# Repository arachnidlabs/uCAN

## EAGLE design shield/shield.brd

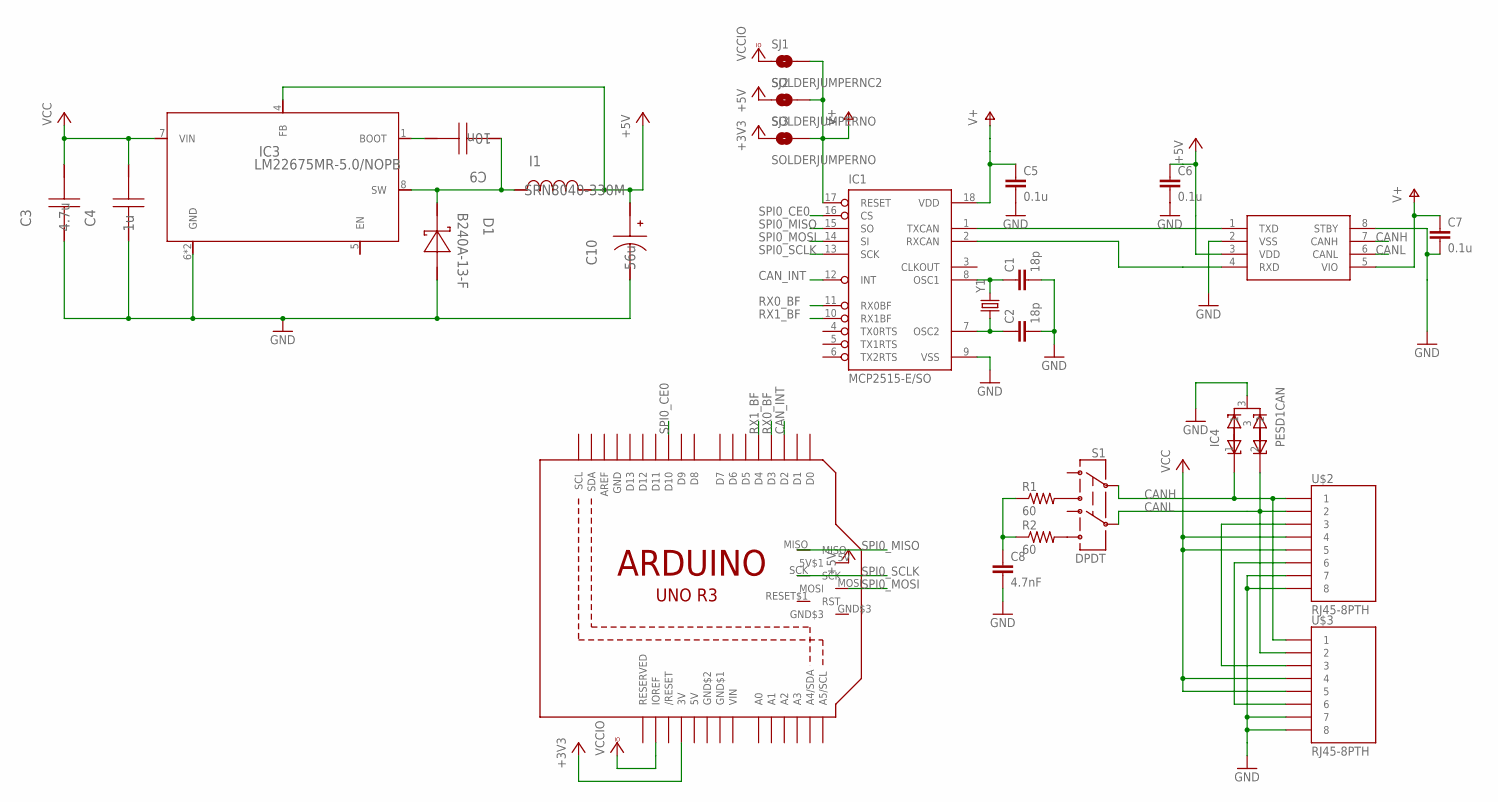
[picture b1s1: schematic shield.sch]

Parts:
C1, C2: 18p; 0603-CAP
C3: 4.7u; 1206
C4: 1u; 0805
C5, C6, C7: 0.1u; 0603-CAP
C8: 4.7nF; 0603-CAP
C9: 10n; 0805
C10: 56u; SM_RADIAL_6.3AMM
D1: B240A-13-F; SMA
I1: SRN8040-330M; SRN8040
IC1: MCP2515-E/SO; SO18L
IC2: MCP2562; SO08
IC3: LM22675MR-5.0/NOPB; MRA08B
IC4: PESD1CAN; SOT23
R1, R2: 60; 0603-RES
S1: DPDT; AYZ0202
SJ1: SOLDERJUMPERNC2; SJ_2S-NOTRACE
SJ2, SJ3: SOLDERJUMPERNO; SJ_2S-NO
U$1: ARDUINO_R3_ICSPNODIM; ARDUINOR3_ICSP_NODIM
U$2, U$3: RJ45-8PTH; RJ45-8
Y1: CRYSTAL5X3; CRYSTAL-SMD-5X3

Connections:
5V: U$1.+5V (5V)
+3V3: SJ3.1, U$1.3V
+5V: C6.1, C10.1 (+), I1.1, IC2.3 (VDD), IC3.4 (FB), SJ2.1, U$1.5V (5V$1)
CANH: IC2.7 (CANH), IC4.1, S1.2, U$2.1, U$3.1
CANL: IC2.6 (CANL), IC4.2, S1.5, U$2.2, U$3.2
CAN_INT: IC1.12 (INT), U$1.D2
GND: C1.2, C2.2, C3.2, C4.2, C5.2, C6.2, C7.2, C8.2, C10.2 (-), D1.2 (A), IC1.9 (VSS), IC2.2 (VSS), IC2.8 (STBY), IC3.6 (GND), IC3.EPAD (GND), IC4.3, U$1.GND, U$2.7, U$2.8, U$3.7, U$3.8
GND$1: U$1.GND$1
GND$2: U$1.GND$2
unnamed: R1.2, S1.3
unnamed: R2.2, S1.6
unnamed: C1.1, IC1.8 (OSC1), Y1.3 (2)
unnamed: C2.1, IC1.7 (OSC2), Y1.1
unnamed: C8.1, R1.1, R2.1
unnamed: U$2.6, U$3.6
unnamed: U$2.3, U$3.3
unnamed: C9.1, IC3.1 (BOOT)
RX0_BF: IC1.11 (RX0BF), U$1.D3
RX1_BF: IC1.10 (RX1BF), U$1.D4
RXCAN: IC1.2 (RXCAN), IC2.4 (RXD)
SPI0_CE0: IC1.16 (CS), U$1.D10
SPI0_MISO: IC1.15 (SO), U$1.MISO
SPI0_MOSI: IC1.14 (SI), U$1.MOSI
SPI0_SCLK: IC1.13 (SCK), U$1.SCK
SWOUT: C9.2, D1.1 (K), I1.2, IC3.8 (SW)
TXCAN: IC1.1 (TXCAN), IC2.1 (TXD)
V+: C5.1, C7.1, IC1.17 (RESET), IC1.18 (VDD), IC2.5 (VIO), SJ1.2, SJ2.2, SJ3.2
VCC: C3.1, C4.1, IC3.7 (VIN), U$2.4, U$2.5, U$3.4, U$3.5
VCCIO: SJ1.1, U$1.IOREF
VIN: U$1.VIN

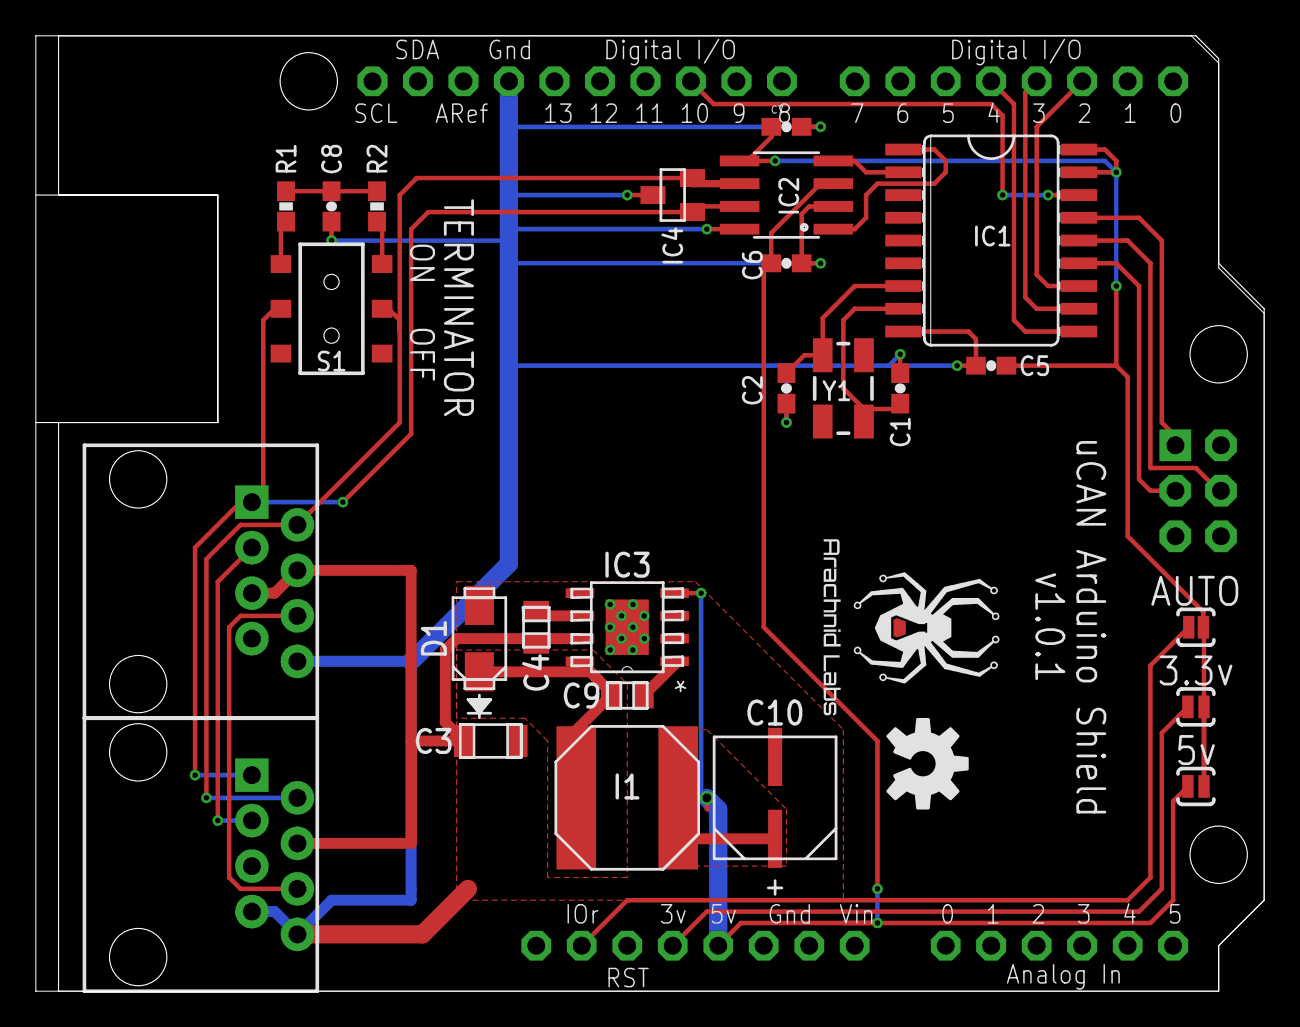
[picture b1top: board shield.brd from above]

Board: 2 copper layers, 68.6 x 53.3 mm, 28 parts (0 on the bottom side), 26 nets.

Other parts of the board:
U$4: ARACHNID_LABS_LOGO_SM
U$5: OSHW-LOGO-M

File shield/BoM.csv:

"Part";"Value";"Device";"Package";"Description";"PROD_ID";"VALUE";
"C1";"18p";"CAP0603-CAP";"0603-CAP";"Capacitor";"";"";
"C2";"18p";"CAP0603-CAP";"0603-CAP";"Capacitor";"";"";
"C3";"";"CAP_POLG";"PANASONIC_G";"Capacitor Polarized";"";"";
"C4";"";"CAP_POLE";"PANASONIC_E";"Capacitor Polarized";"";"";
"C5";"0.1u";"CAP0603-CAP";"0603-CAP";"Capacitor";"";"";
"C6";"0.1u";"CAP0603-CAP";"0603-CAP";"Capacitor";"";"";
"C7";"0.1u";"CAP0603-CAP";"0603-CAP";"Capacitor";"";"";
"C8";"4.7nF";"CAP0603-CAP";"0603-CAP";"Capacitor";"";"";
"D1";"";"DIODESMA-ALT";"SMA-DIODE_ALT";"Diode";"";"";
"IC1";"MCP2515-E/SO";"MCP2515-E/SO";"SO18L";"";"";"";
"IC2";"MCP2562";"MCP2562";"SO08";"CAN transceiver";"";"";
"IC3";"LM2595NDH";"LM2595NDH";"TO263-5";"";"";"";
"IC4";"PESD1CAN";"PESD1CAN";"SOT23";"";"";"";
"L1";"MSS1260";"MSS1260";"MSS1260";"";"";"";
"R1";"60";"RESISTOR0603-RES";"0603-RES";"Resistor";"";"";
"R2";"60";"RESISTOR0603-RES";"0603-RES";"Resistor";"";"";
"S1";"DPDT";"SWITCH-DPDTAYZ0202";"AYZ0202";"DPDT Version of the COM-00597";"SWCH-08179";"DPDT";
"SJ1";"SOLDERJUMPERNC2";"SOLDERJUMPERNC2";"SJ_2S-NOTRACE";"Solder Jumper";"";"";
"SJ2";"SOLDERJUMPERNO";"SOLDERJUMPERNO";"SJ_2S-NO";"Solder Jumper";"";"";
"SJ3";"SOLDERJUMPERNO";"SOLDERJUMPERNO";"SJ_2S-NO";"Solder Jumper";"";"";
"U$1";"ARDUINO_R3_ICSP";"ARDUINO_R3_ICSP";"ARDUINOR3_ICSP";"";"";"";
"U$2";"RJ45-8PTH";"RJ45-8PTH";"RJ45-8";"RJ45 Jack";"";"";
"U$3";"RJ45-8PTH";"RJ45-8PTH";"RJ45-8";"RJ45 Jack";"";"";
"Y1";"";"CRYSTAL5X3";"CRYSTAL-SMD-5X3";"Various standard crystals. Proven footprints. Spark Fun Electronics SKU : COM-00534";"";"";

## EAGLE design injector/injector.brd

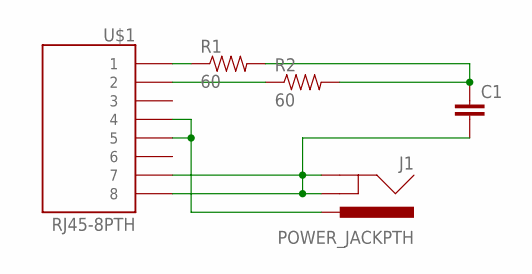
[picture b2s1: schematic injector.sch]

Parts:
C1: CAP0603-CAP; 0603-CAP
J1: POWER_JACKPTH; POWER_JACK_PTH
R1, R2: 60; 0603-RES
U$1: RJ45-8PTH; RJ45-8

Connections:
unnamed: R1.1, U$1.1
unnamed: R2.1, U$1.2
unnamed: J1.PWR, U$1.4, U$1.5
unnamed: C1.2, J1.GND, J1.GNDBREAK, U$1.7, U$1.8
unnamed: C1.1, R1.2, R2.2

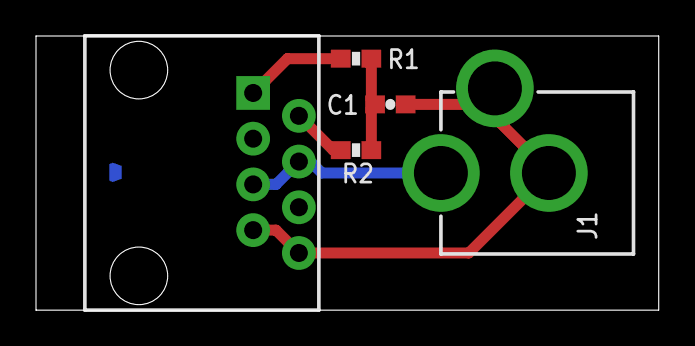
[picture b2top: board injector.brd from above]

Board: 2 copper layers, 34.6 x 15.2 mm, 6 parts (1 on the bottom side), 5 nets.

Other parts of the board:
U$2: ARACHNID_LABS_LOGO_SM

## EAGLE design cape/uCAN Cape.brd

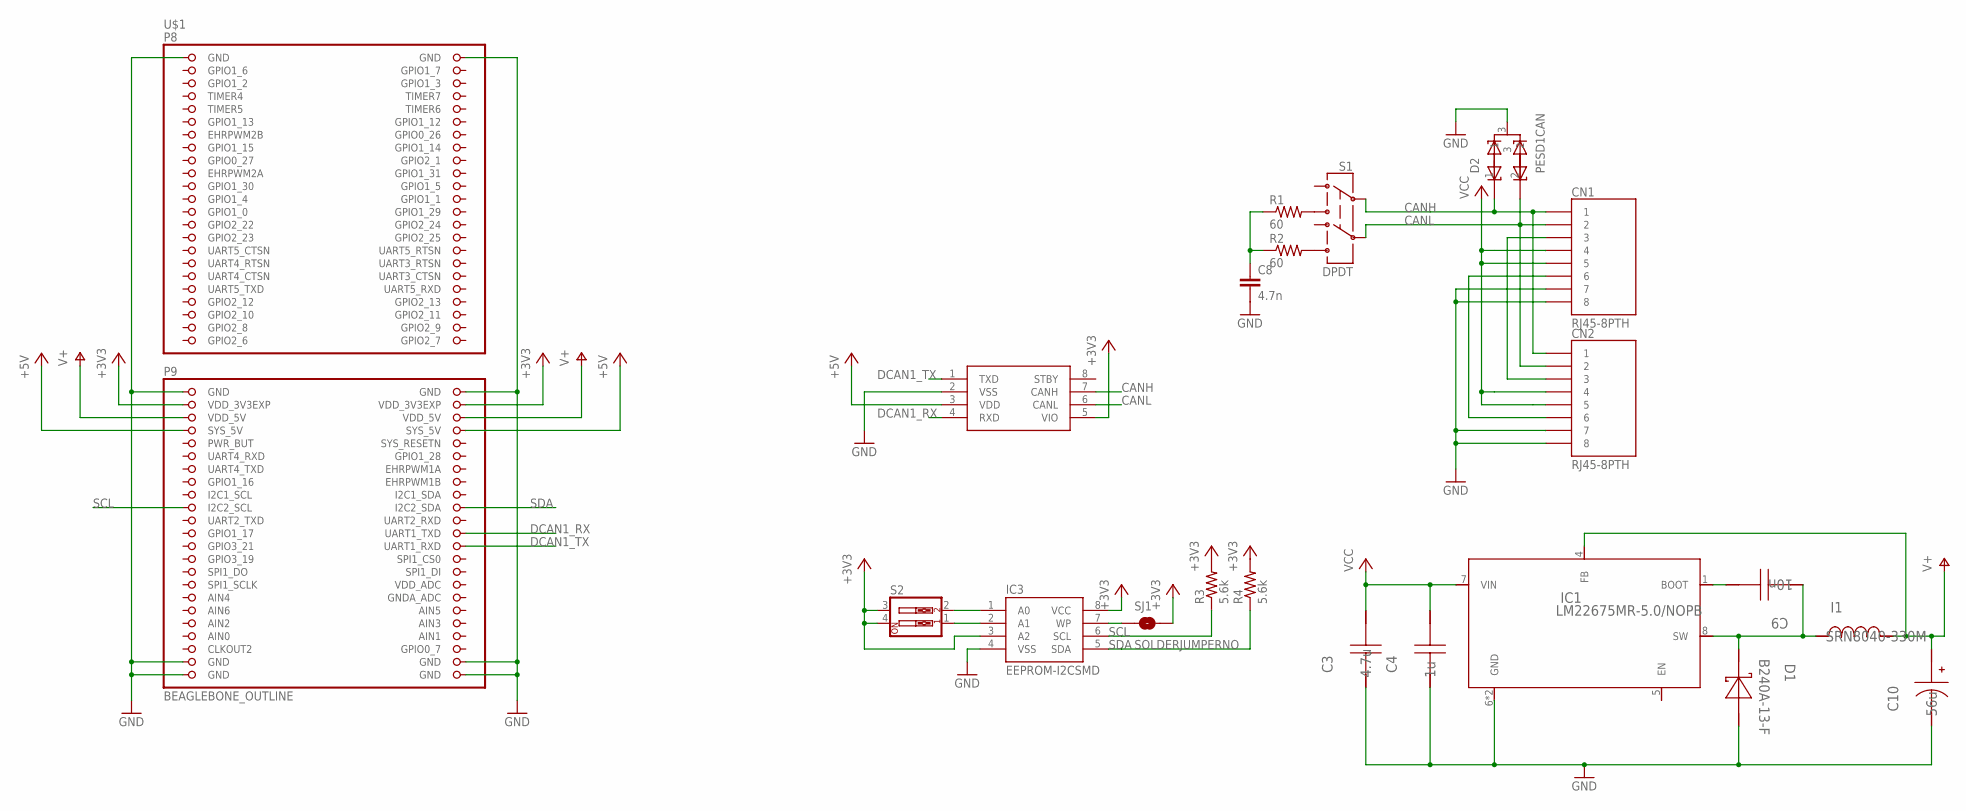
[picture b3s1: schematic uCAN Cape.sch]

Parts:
C3: 4.7u; 1206
C4: 1u; 0805
C8: 4.7n; 0603-CAP
C9: 10n; 0805
C10: 56u; SM_RADIAL_6.3AMM
CN1, CN2: RJ45-8PTH; RJ45-8
D1: B240A-13-F; SMA
D2: PESD1CAN; SOT23
I1: SRN8040-330M; SRN8040
IC1: LM22675MR-5.0/NOPB; MRA08B
IC2: MCP2562; SO08
IC3: EEPROM-I2CSMD; SO08
R1, R2: 60; 0603-RES
R3, R4: 5.6k; 0603-RES
S1: DPDT; AYZ0202
S2: SW_DIP-2; DIPSWITCH-02
SJ1: SOLDERJUMPERNO; SJ_2S-NO
U$1: BEAGLEBONE_OUTLINE; BEAGLEBONE_SHIELD

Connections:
+3V3: IC2.5 (VIO), IC3.3 (A2), IC3.8 (VCC), R3.2, R4.2, S2.3, S2.4, SJ1.2, U$1.49 (VDD_3V3EXP), U$1.50 (VDD_3V3EXP)
+5V: IC2.3 (VDD), U$1.53 (SYS_5V), U$1.54 (SYS_5V)
A0: IC3.1 (A0), S2.2
A1: IC3.2 (A1), S2.1
AIN0: U$1.85 (AIN0)
CANH: CN1.1, CN2.1, D2.1, IC2.7 (CANH), S1.2
CANL: CN1.2, CN2.2, D2.2, IC2.6 (CANL), S1.5
DCAN1_RX: IC2.4 (RXD), U$1.70 (UART1_TXD)
DCAN1_TX: IC2.1 (TXD), U$1.72 (UART1_RXD)
GND: C3.2, C4.2, C8.2, C10.2 (-), CN1.7, CN1.8, CN2.7, CN2.8, D1.2 (A), D2.3, IC1.6 (GND), IC1.EPAD (GND), IC2.2 (VSS), IC3.4 (VSS), U$1.1 (GND), U$1.2 (GND), U$1.47 (GND), U$1.48 (GND), U$1.89 (GND), U$1.90 (GND), U$1.91 (GND), U$1.92 (GND)
unnamed: R1.2, S1.3
unnamed: IC3.7 (WP), SJ1.1
unnamed: R2.2, S1.6
unnamed: C8.1, R1.1, R2.1
unnamed: CN1.3, CN2.3
unnamed: C9.1, IC1.1 (BOOT)
unnamed: CN1.6, CN2.6
SCL: IC3.6 (SCL), R3.1, U$1.65 (I2C2_SCL)
SDA: IC3.5 (SDA), R4.1, U$1.66 (I2C2_SDA)
SWOUT: C9.2, D1.1 (K), I1.2, IC1.8 (SW)
V+: C10.1 (+), I1.1, IC1.4 (FB), U$1.51 (VDD_5V), U$1.52 (VDD_5V)
VCC: C3.1, C4.1, CN1.4, CN1.5, CN2.4, CN2.5, IC1.7 (VIN)

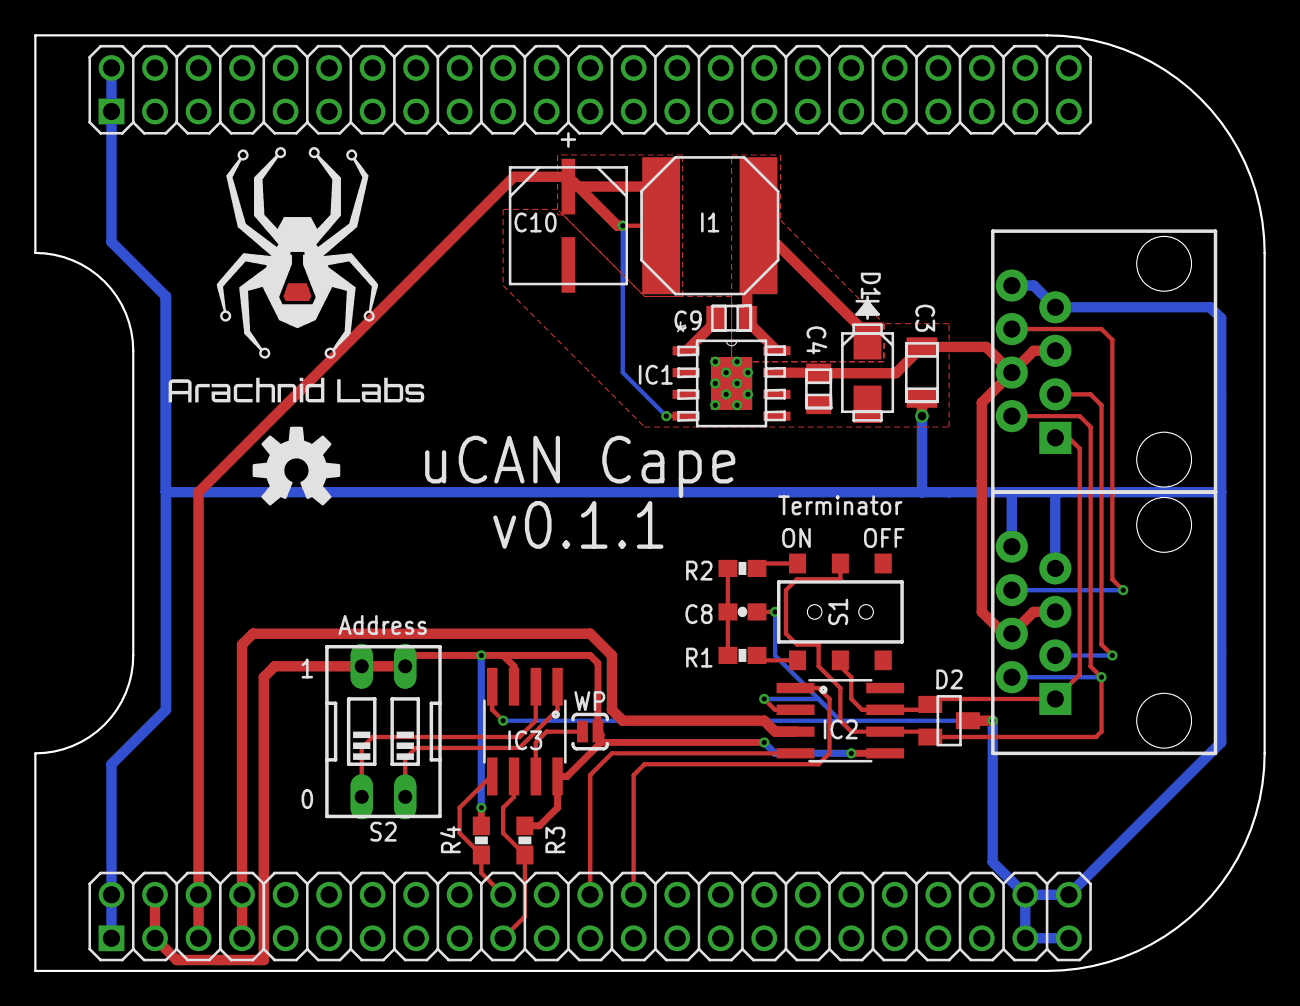
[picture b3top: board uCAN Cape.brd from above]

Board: 2 copper layers, 71.8 x 54.6 mm, 23 parts (0 on the bottom side), 21 nets.

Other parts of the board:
U$2: ARACHNID_LABS_LOGO
U$3: OSHW-LOGO-M

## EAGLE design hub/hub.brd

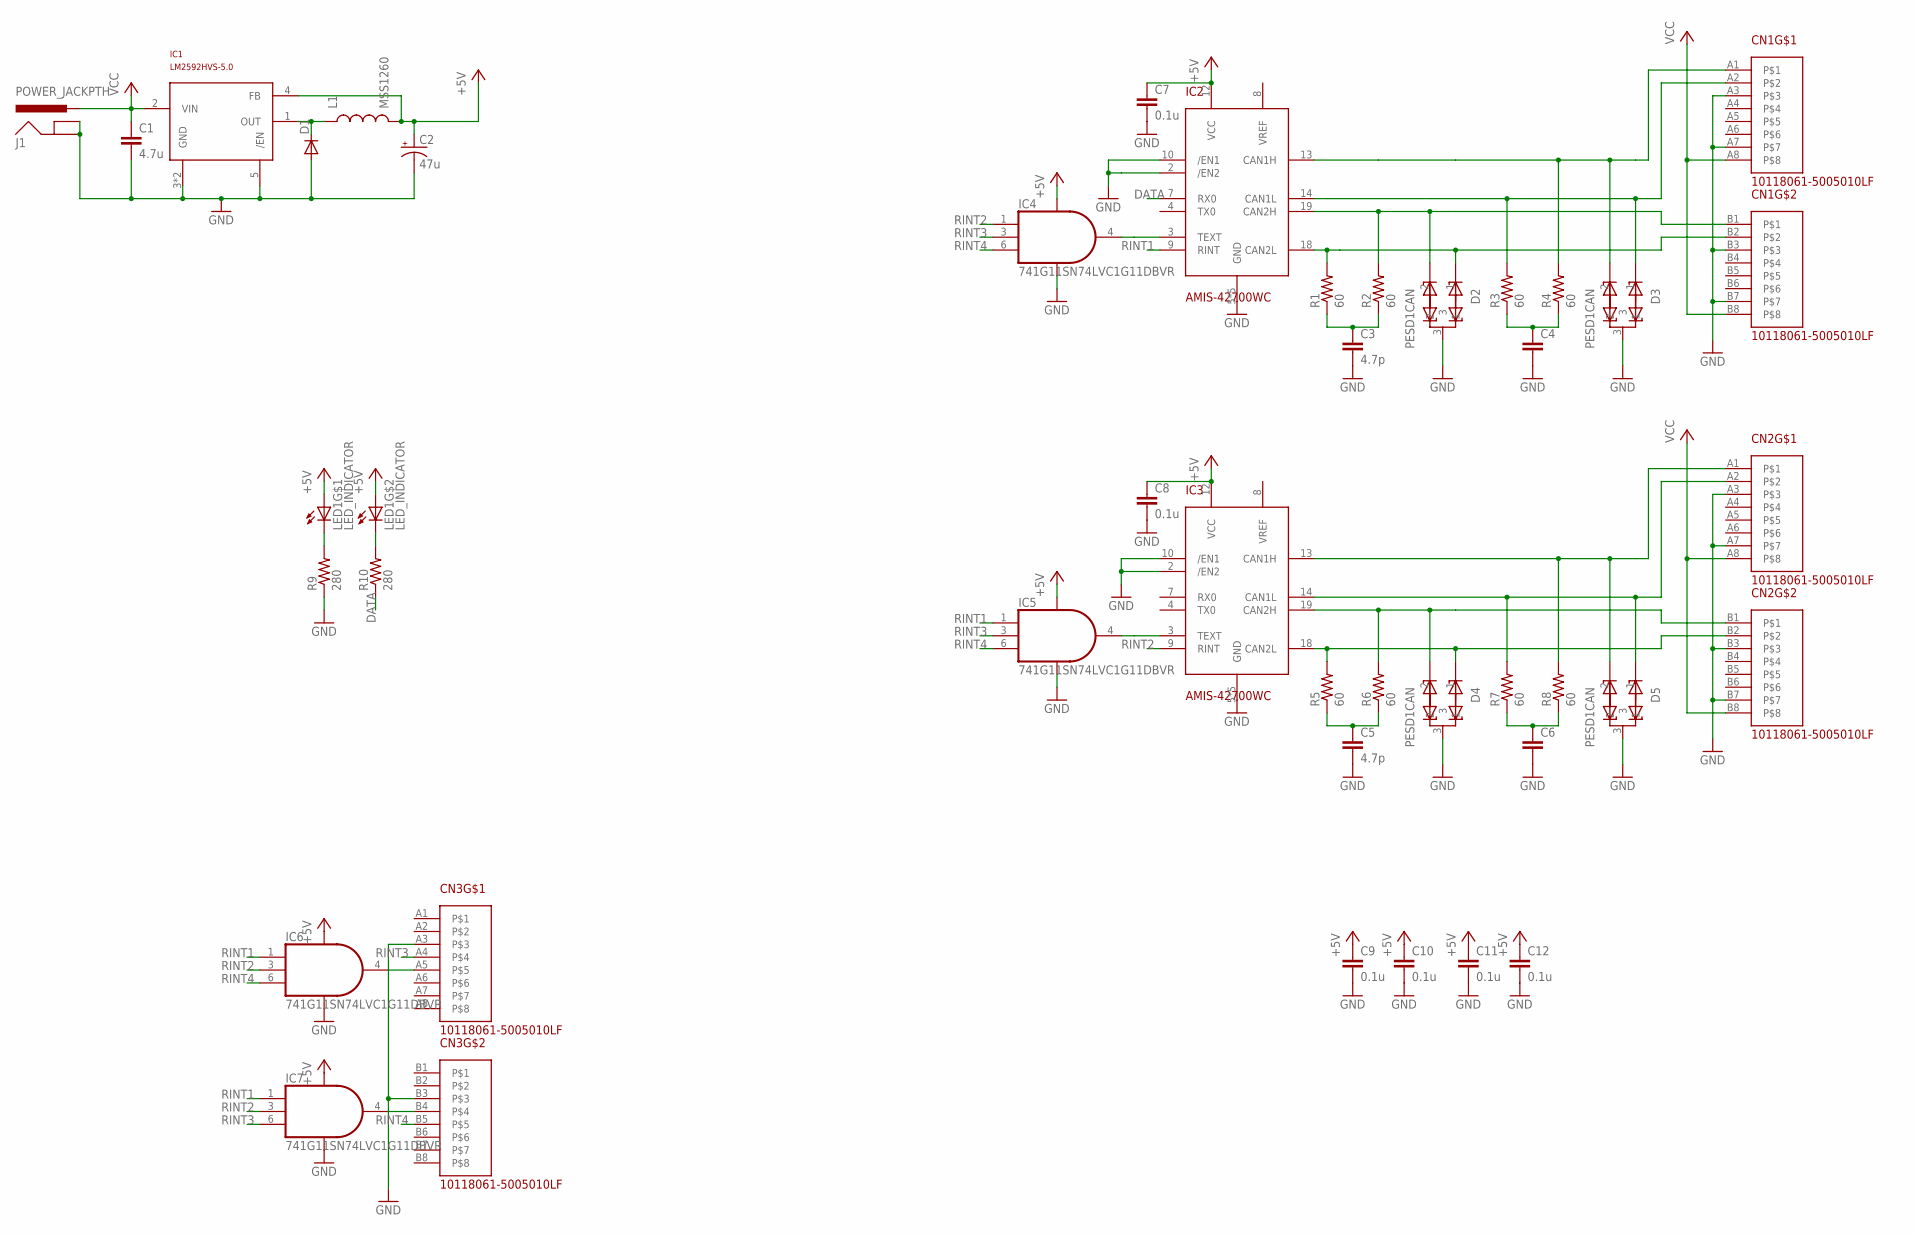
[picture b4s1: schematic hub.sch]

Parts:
C1: 4.7u; 1206
C2: 47u; PANASONIC_C
C3, C5: 4.7p; 0603-CAP
C4, C6: CAP0603-CAP; 0603-CAP
C7, C8, C9, C10, C11, C12: 0.1u; 0603-CAP
CN1, CN2, CN3: 10118061-5005010LF; 10118061
D1: DIODESMA-ALT; SMA-DIODE_ALT
D2, D3, D4, D5: PESD1CAN; SOT23
IC1: LM2592HVS-5.0; TO263-5
IC2, IC3: AMIS-42700WC; SO20W
IC4, IC5, IC6, IC7: 741G11SN74LVC1G11DBVR; SOT23-6
J1: POWER_JACKPTH; POWER_JACK_PTH
L1: MSS1260
LED1: LED_INDICATOR
R1, R2, R3, R4, R5, R6, R7, R8: 60; 0603-RES
R9, R10: 280; 0603-RES

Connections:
+5V: C2.+, C7.1, C8.1, C9.1, C10.1, C11.1, C12.1, IC1.4 (FB), IC2.12 (VCC), IC3.12 (VCC), IC4.5 (VCC), IC5.5 (VCC), IC6.5 (VCC), IC7.5 (VCC), L1.P$2 (2), LED1.A1 (A), LED1.A2 (A)
CAN1H: CN1.A1, D3.2, IC2.13 (CAN1H), R4.2
CAN1L: CN1.A2, D3.1, IC2.14 (CAN1L), R3.2
CAN2H: CN1.B1, D2.2, IC2.19 (CAN2H), R2.2
CAN2L: CN1.B2, D2.1, IC2.18 (CAN2L), R1.2
CAN3H: CN2.A1, D5.2, IC3.13 (CAN1H), R8.2
CAN3L: CN2.A2, D5.1, IC3.14 (CAN1L), R7.2
CAN4H: CN2.B1, D4.2, IC3.19 (CAN2H), R6.2
CAN4L: CN2.B2, D4.1, IC3.18 (CAN2L), R5.2
DATA: IC2.7 (RX0), R10.1
GND: C1.2, C2.-, C3.2, C4.2, C5.2, C6.2, C7.2, C8.2, C9.2, C10.2, C11.2, C12.2, CN1.A3, CN1.A7, CN1.B3, CN1.B7, CN2.A3, CN2.A7, CN2.B3, CN2.B7, CN3.A3, CN3.B3, D1.A, D2.3, D3.3, D4.3, D5.3, IC1.3 (GND), IC1.5 (/EN), IC1.6 (GND), IC2.2 (/EN2), IC2.5 (GND), IC2.6 (GND), IC2.10 (/EN1), IC2.15 (GND), IC2.16 (GND), IC2.17 (GND), IC3.2 (/EN2), IC3.5 (GND), IC3.6 (GND), IC3.10 (/EN1), IC3.15 (GND), IC3.16 (GND), IC3.17 (GND), IC4.2 (GND), IC5.2 (GND), IC6.2 (GND), IC7.2 (GND), J1.GND, J1.GNDBREAK, R9.1
unnamed: IC2.3 (TEXT), IC4.4 (O)
unnamed: C3.1, R1.1, R2.1
unnamed: C4.1, R3.1, R4.1
unnamed: IC3.3 (TEXT), IC5.4 (O)
unnamed: C5.1, R5.1, R6.1
unnamed: C6.1, R7.1, R8.1
unnamed: CN3.A5, IC6.4 (O)
unnamed: CN3.B4, IC7.4 (O)
unnamed: LED1.C1 (C), R9.2
unnamed: LED1.C2 (C), R10.2
RINT1: IC2.9 (RINT), IC5.1 (I0), IC6.1 (I0), IC7.1 (I0)
RINT2: IC3.9 (RINT), IC4.1 (I0), IC6.3 (I1), IC7.3 (I1)
RINT3: CN3.A4, IC4.3 (I1), IC5.3 (I1), IC7.6 (I2)
RINT4: CN3.B5, IC4.6 (I2), IC5.6 (I2), IC6.6 (I2)
SWOUT: D1.C, IC1.1 (OUT), L1.P$1 (1)
VCC: C1.1, CN1.A8, CN1.B8, CN2.A8, CN2.B8, IC1.2 (VIN), J1.PWR

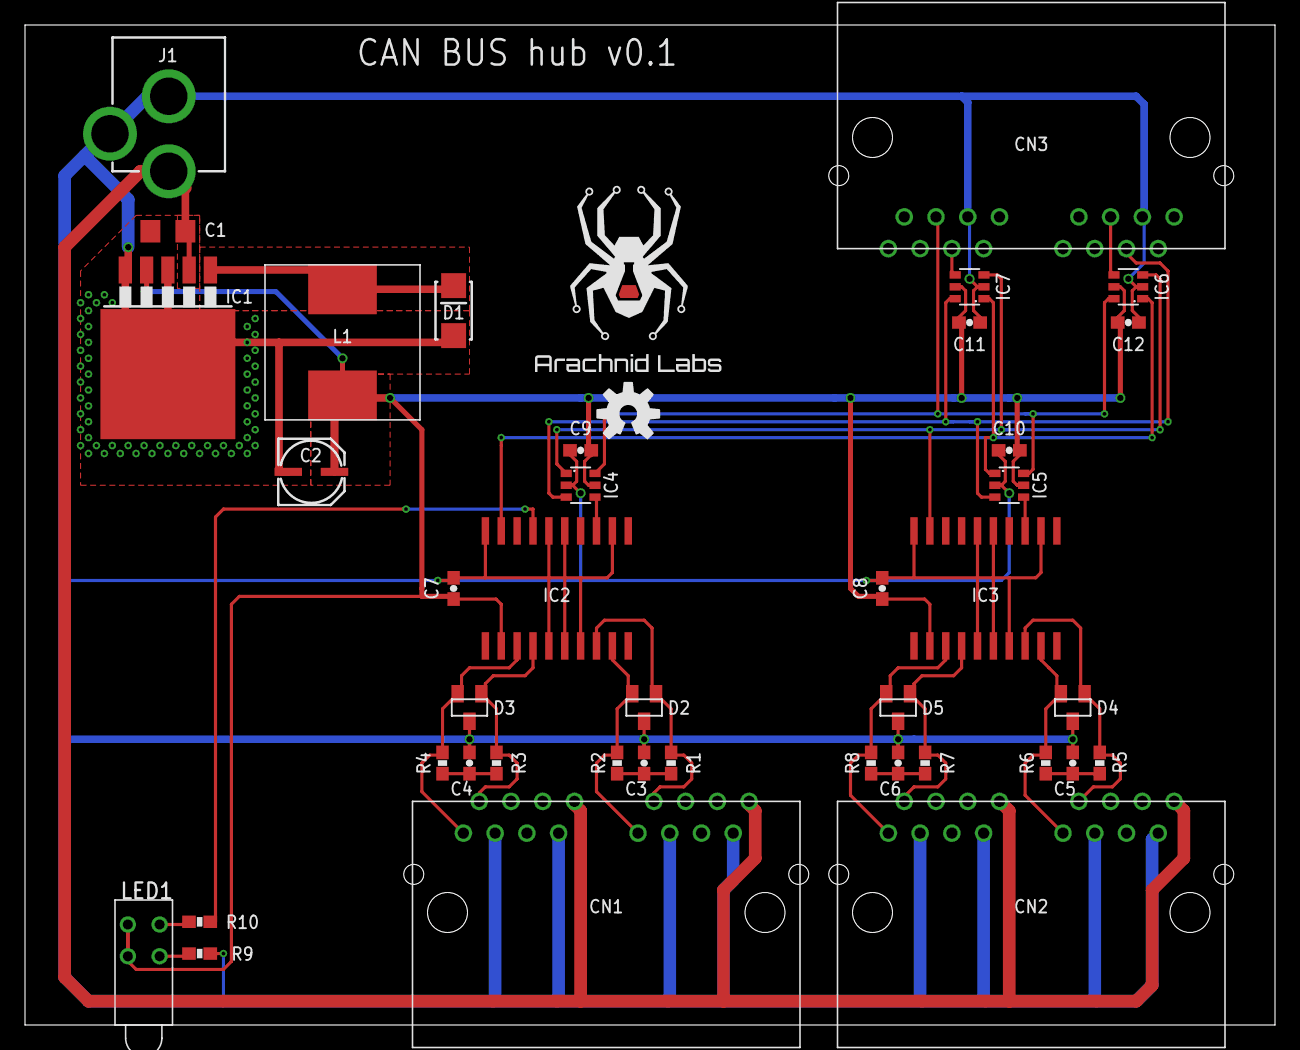
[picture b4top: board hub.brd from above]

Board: 2 copper layers, 100.0 x 80.0 mm, 42 parts (0 on the bottom side), 27 nets.

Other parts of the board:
U$1: ARACHNID_LABS_LOGO
U$2: OSHW-LOGO-M

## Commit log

2013-10-08 Added front and back renders
2013-10-09 Added power injector board; refactored boards to use MCP2562 instead of MCP2551
2013-10-10 Switch to split termination with a switch
2013-10-10 Modify injector for split termination
2013-10-10 Added TVS diodes, fixed silkscreen issues
2013-10-26 Hub schematic
2013-10-27 Added beaglebone cape
2013-11-20 Added new hub design
2013-11-20 Minor changes to shield, rpi board, and cape
2013-11-20 Added uCAN Arduino Library

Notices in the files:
parts and their libraries:
SparkFun-DigitalIC: Licensing: CC v3.0 Share-Alike You are welcome to use this library for commercial purposes.
